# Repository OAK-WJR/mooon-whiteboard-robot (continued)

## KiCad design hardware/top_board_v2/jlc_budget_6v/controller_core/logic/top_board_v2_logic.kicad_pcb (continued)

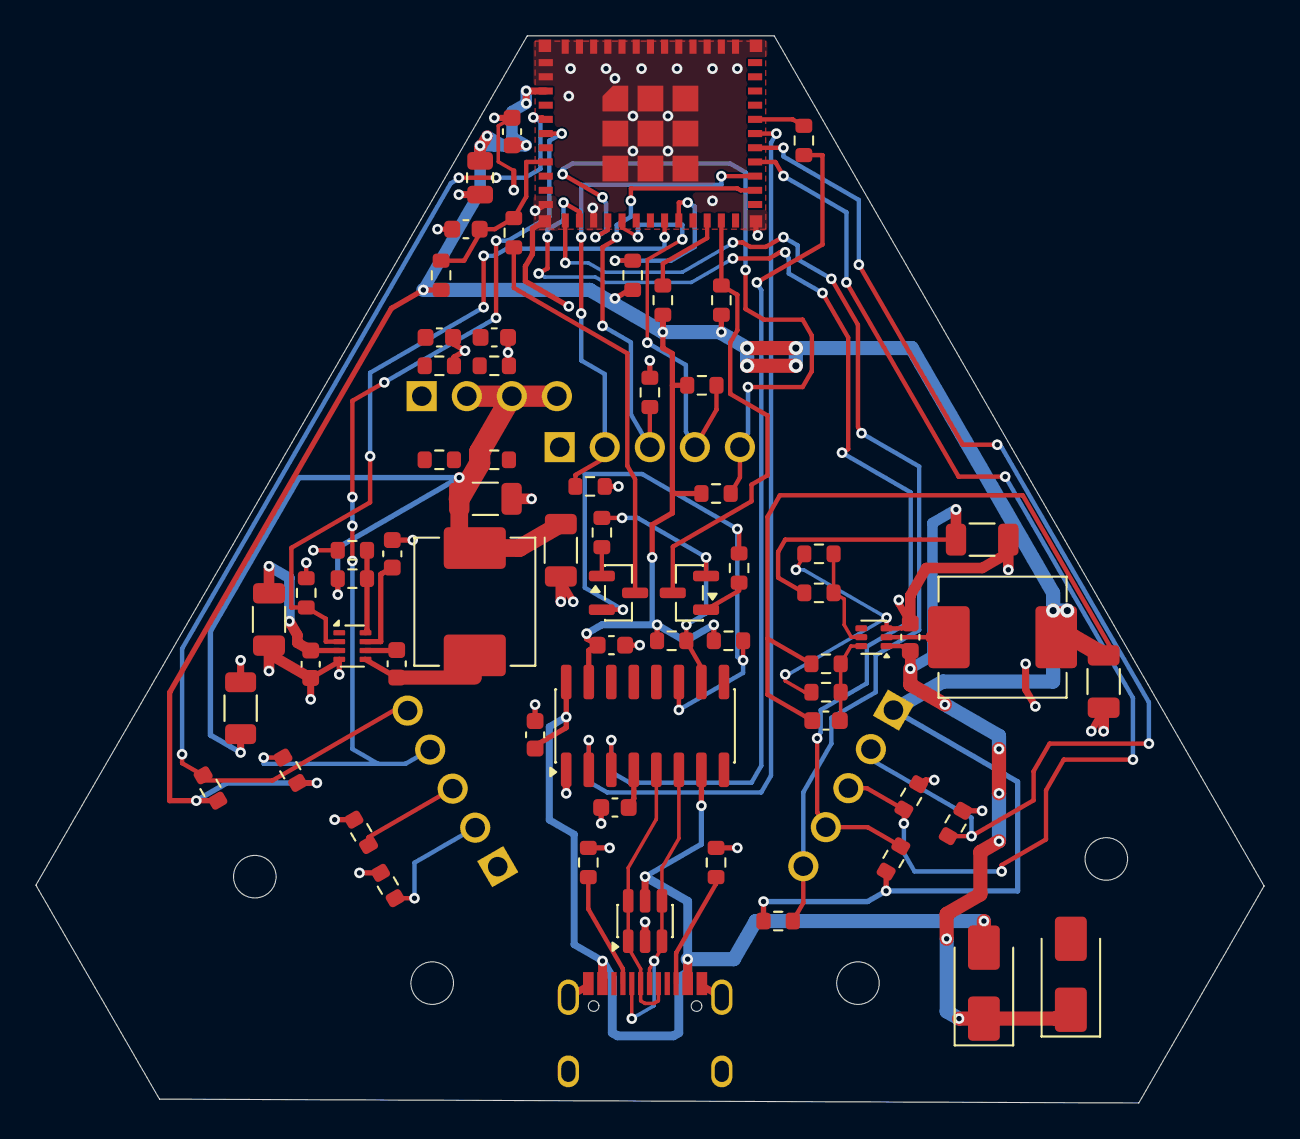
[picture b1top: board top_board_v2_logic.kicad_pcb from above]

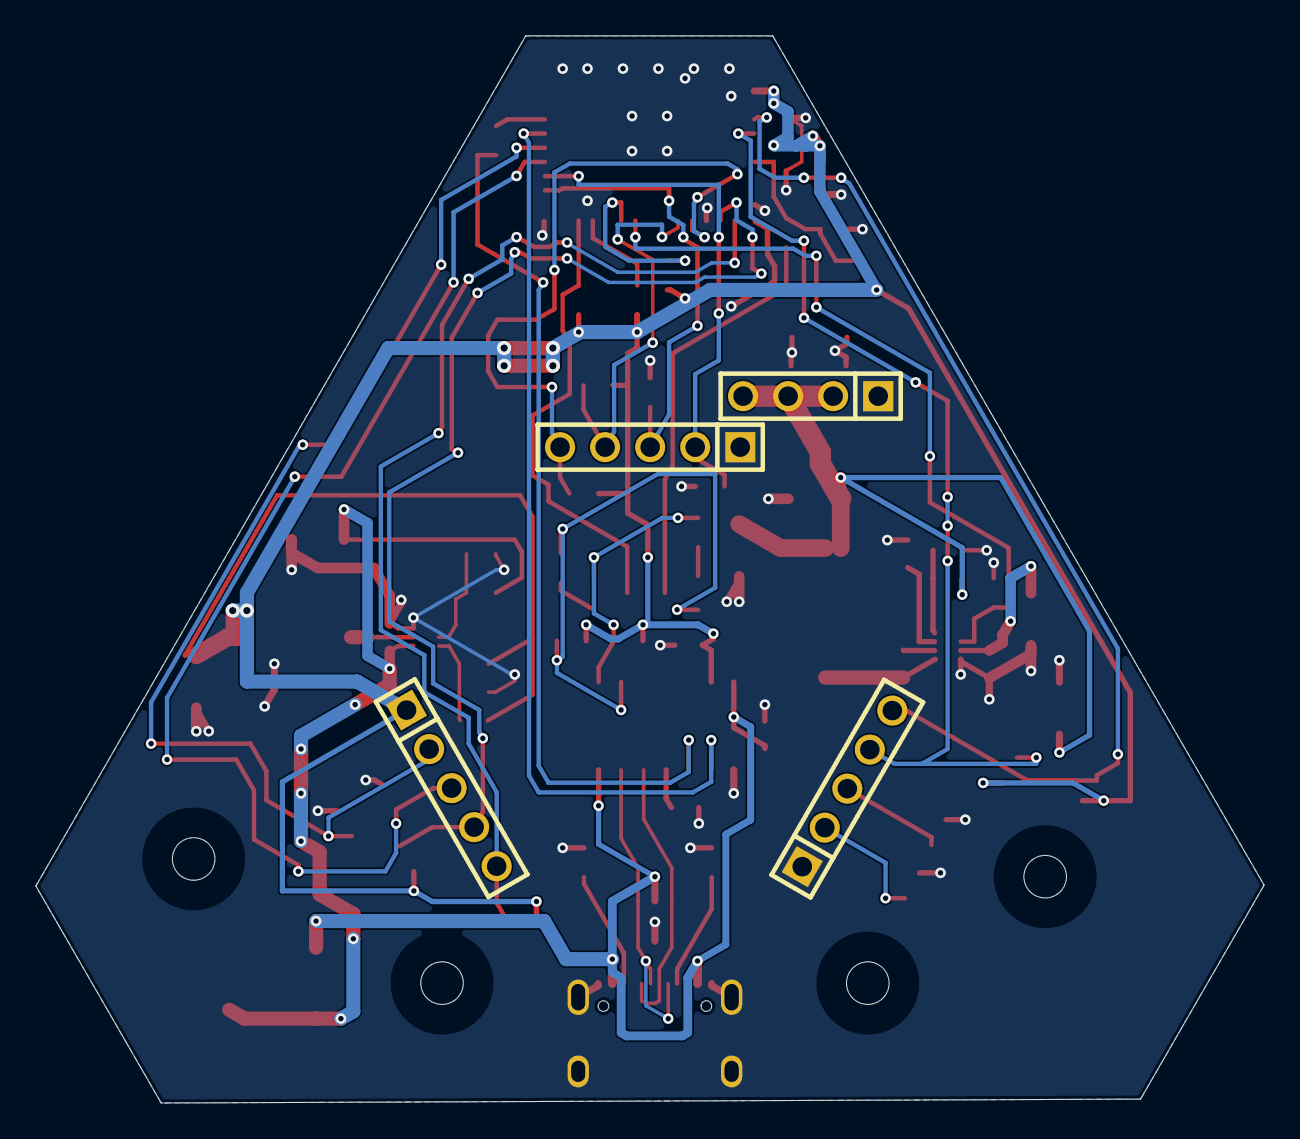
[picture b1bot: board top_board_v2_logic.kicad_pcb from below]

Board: 2 copper layers, 69.2 x 60.2 mm, 74 parts (4 on the bottom side), 45 nets.

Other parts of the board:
MH1, MH2, MH3, MH4: M2 carrier reserve: NPTH 2.4 / boss 6.0; Carrier_M2_NPTH_2.4mm_Reserve_6mm

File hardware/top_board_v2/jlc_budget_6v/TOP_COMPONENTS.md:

# List of components drawn on the top board

Exported from the current six-page KiCad netlist: 70 components per board, 350 for five boards.

Of these, 63 references have store part numbers and 7 are not yet assigned. This is a list of drawn components, not a full purchasing BOM or a finished-board quote. Having a part number also does not mean assembly and electrical verification are done.

**Scope is only the five top PCBs, the components on them and soldering.** The base board, motors, battery, charger and external accessories are not counted. The final input connector and protection are not drawn yet; undecided USB and ADC behavior may also affect the final list.

| Reference | Value in drawing | JLCPCB part number filled in | Per board | Five boards |
| --- | --- | --- | ---: | ---: |
| C1, C2, C3, C6, C8, C15, C16, C17, C20, C21 | 100n 50V X7R 10% | C14663 | 10 | 50 |
| C4 | 1u 10V X7R | TBD | 1 | 5 |
| C5 | 10u 10V X7R | TBD | 1 | 5 |
| C7, C11, C14, C18, C19 | 22u 25V X5R 10% | C12891 | 5 | 25 |
| C9 | 33p 50V C0G 5% | C1663 | 1 | 5 |
| D1, D2 | SS14 / REVIEW | C2480 | 2 | 10 |
| L1 | 2.2u 20% | C408445 | 1 | 5 |
| L2 | 4.7u 20% | C408447 | 1 | 5 |
| M0, M1, M2 | PZ254V-11-05P | C492404 | 3 | 15 |
| PWR1 | PZ254V-11-04P | C2691448 | 1 | 5 |
| Q1, Q2 | MMBT3904 | TBD | 2 | 10 |
| R1, R2 | 5.1k 1% | C23186 | 2 | 10 |
| R3, R4, R9, R10, R14, R15, R18, R19, R22, R23, R24, R25, R29, R31, R32, R34, R36 | 10k 1% | C25804 | 17 | 85 |
| R5 | 680 1% | C23228 | 1 | 5 |
| R6, R7, R12, R13, R16, R17, R20, R21 | 4.7k 1% | C23162 | 8 | 40 |
| R8 | 22k 1% | C31850 | 1 | 5 |
| R11 | 499 1% | TBD | 1 | 5 |
| R26 | 135k 1% | TBD | 1 | 5 |
| R27 | 30k 1% | C22984 | 1 | 5 |
| R28 | 64.9k 1% | C14891 | 1 | 5 |
| R30 | 470 1% 0.25W | TBD | 1 | 5 |
| R33, R35 | 120k 1% | C25808 | 2 | 10 |
| U1 | CH343G | C2844153 | 1 | 5 |
| U2 | USBLC6-2SC6 | C7519 | 1 | 5 |
| U3 | ESP32-C6-MINI-1-N4 | C5736265 | 1 | 5 |
| U4 | TPS563252DRLR | C19188399 | 1 | 5 |
| U5 | TPS62933DRLR | C3200405 | 1 | 5 |
| USB1 | TYPE-C-31-M-12 | C165948 | 1 | 5 |

Quantities are placement use, without retail minimum order quantities, loss or spares. All unquoted items stay unknown and are not counted as zero in the total.

[Footprints, fields and source file hashes per reference](top_component_inventory.json) · [Cost review](COST_REVIEW.md) · [Six-page schematic](controller_core/logic/top_board_v2_review.pdf)

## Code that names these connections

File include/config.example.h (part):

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// Note: the measured pairing of adapter-board headers to base-board sockets is crossed: M0 header -> base H2 (motor 1),
//       M1 header -> base H1 (motor 3), M2 header -> base H3 (motor 2). So pins here are bound in physical motor order,
//       [1] uses the M2 header pins and [2] uses the M1 header pins; the kinematics matrix needs no change.
// C6 pins not to use: GPIO12/13 (USB-Serial/JTAG flashing), GPIO9 (BOOT), 6/7/8/14/15/21/22 (used by the display board)

// Motor 0 = physical Motor1 (via adapter M0 header -> base H2 -> controller1)
#define MOTOR0_FI_PIN       0        // GPIO0
#define MOTOR0_BI_PIN       1        // GPIO1

// Motor 1 = physical Motor2 (via adapter M2 header -> base H3 -> controller2)
#define MOTOR1_FI_PIN       4        // GPIO4
#define MOTOR1_BI_PIN       5        // GPIO5

// Motor 2 = physical Motor3 (via adapter M1 header -> base H1 -> controller3)
#define MOTOR2_FI_PIN       2        // GPIO2
#define MOTOR2_BI_PIN       3        // GPIO3

// --- Encoder pins (A/B phase), also in physical motor order ---
#ifdef WBB_TOP_BOARD_V2
#define ENC0_A_PIN          7        // New integrated board: GPIO16 remains UART TX.
#else
#define ENC0_A_PIN          16       // GPIO16 (UART0 TXD, 100Ω series resistor on adapter board)
#endif
#define ENC0_B_PIN          17       // GPIO17 (UART0 RXD)
#define ENC1_A_PIN          20       // GPIO20  <- M2 header
#define ENC1_B_PIN          23       // GPIO23  <- M2 header
#define ENC2_A_PIN          18       // GPIO18  <- M1 header
#define ENC2_B_PIN          19       // GPIO19  <- M1 header

#else
// ===================== ESP32 (old all-in-one board, kept for fallback) =====================
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
// Motor 2 (controller3, Motor3)
#define MOTOR2_FI_PIN       27       // GPIO27 - controller3 FI (forward input)
#define MOTOR2_BI_PIN       14       // GPIO14 - controller3 BI (reverse input)

// --- Encoder pins (A/B phase) ---
// motor0 encoder (Motor1 connector) - confirmed by measurement
#define ENC0_A_PIN          34       // GPIO34 - Motor1 Enc A (input only, no internal pull-up)
#define ENC0_B_PIN          35       // GPIO35 - Motor1 Enc B (input only, no internal pull-up)
// motor1 encoder (Motor2 connector) - v2 board reroutes to GPIO22/23 (regular pins, with internal pull-up)
#define ENC1_A_PIN          22       // GPIO22 - Motor2 Enc A (internal pull-up, no external resistor)
#define ENC1_B_PIN          23       // GPIO23 - Motor2 Enc B (internal pull-up, no external resistor)
// motor2 encoder (Motor3 connector) - confirmed by measurement
#define ENC2_A_PIN          19       // GPIO19 - Motor3 Enc A
#define ENC2_B_PIN          18       // GPIO18 - Motor3 Enc B
#endif

// --- Encoder direction correction ---
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
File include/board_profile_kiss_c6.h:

#pragma once
// C6-MINI top schematic; power/PCB/harness not released.
#if !defined(WBB_TOP_BOARD_KISS_C6) || WBB_TOP_BOARD_KISS_C6 != 1
#error "Select the explicit top_board_v2_kiss_c6 environment"
#endif
#if defined(WBB_TOP_BOARD_R3) || defined(WBB_TOP_BOARD_PICO)
#error "KISS C6 cannot be combined with another board profile"
#endif
#if !defined(CONFIG_IDF_TARGET_ESP32C6) || !CONFIG_IDF_TARGET_ESP32C6 || defined(CONFIG_IDF_TARGET_ESP32S3)
#error "KISS C6 requires ESP32-C6"
#endif
#if !defined(WBB_TOP_BOARD_V2) || WBB_TOP_BOARD_V2 != 1 || defined(WBB_R3_DIAGNOSTIC) || defined(MOTOR_TEST_MODE)
#error "KISS C6 requires the gated integrated runtime"
#endif
#if !defined(ARDUINO_USB_CDC_ON_BOOT) || ARDUINO_USB_CDC_ON_BOOT != 1
#error "KISS C6 has no USB-UART bridge (CH343G removed 2026-10-29): Serial is the C6's native USB CDC"
#endif

#include <stdint.h>
namespace kiss_c6 {
constexpr const char* profile = "top_board_v2_kiss_c6_review";
// GPIO map follows the 2026-10-27 escape re-route: each header takes the module pads nearest to it.
constexpr int motorArmRequest = 0;
// Factory ADC conversion uses these pins. Divider calibration/off-state review pending.
// batterySense: VBAT divider (120k/10k). motorSense (2026-10-28 board rev): total motor current from INA180A1
// (gain 20) on the 0.1 ohm VMOT shunt R49, via 1k/100nF -> 2.0 V per A. Linear (datasheet gain error) to ~1.4 A
// (VOUT <= VS-0.5 V); the output rails near 3.27 V (~1.6 A). It is no longer VMOT.
constexpr int batterySense = 4, motorSense = 5;
// Sensor head (J1), 2026-10-29: GPIO12/13 are the native USB again, so I2C SDA moved to the GPIO15 strap (sampled
// only if the JTAG-select eFuse is burned) and SCL to GPIO16 (the ROM boot log toggles it with SDA high: no START).
// The IR LED switch moved to GPIO17, which stays quiet at boot; R25 still pulls it up (IR off).
constexpr int i2cSda = 15, i2cScl = 16, irEnableN = 17;
// USB power sense (2026-10-29): VBUS -> R52 1k -> USB_DIV -> R10 2.2k -> GND, isolated from IO8 by Q1 (2N7002, gate 3V3,
// drain USB_DIV, source IO8) with R53 100k IO8 -> 3V3. USB present: USB_DIV ~3.4 V (3.0 V at a 4.4 V sag), Q1 off, IO8 = 3.3 V.
// No USB: VBUS floats except for D1's reverse leakage (SS14, up to ~0.3 mA hot), which the stiff divider turns into <=0.66 V,
// so Q1 conducts and IO8 <= 0.72 V (< VIL 0.825 V). 3V3 off while charging: Q1 off, nothing drives the unpowered IO8.
// IO8 is a strap that only matters for manual download mode, which always has USB plugged in (so it reads high).
// The board reports "battery" vs "external_power" over USB and Wi-Fi; whether the IP2326 is still charging is not
// observable (no charger status pin reaches the MCU). Charging draws ~1.2 A at 5 V (0.6 A into the 2S pack). Since
// 2026-10-30 a CC gate (LM393 U8 vs a 0.65 V CJ431 threshold, Q2 on IP2326 EN) enables charging only on a USB-C source
// advertising >=1.5 A; a Default-USB source or a USB-A cable powers the board but does not charge.
constexpr int usbPowerSense = 8;
struct MotorPins { uint8_t fi, bi, encA, encB, physical; const char* header; };
constexpr MotorPins headers[] = {
    {22, 23, 20, 21, 1, "M0"},
    {1, 6, 2, 3, 3, "M1"},
    {14, 7, 19, 18, 2, "M2"},
};
constexpr int physicalOrder[] = {0, 2, 1};
constexpr bool isMotorPin(int pin) {
    for (const auto& p : headers) if (pin == p.fi || pin == p.bi) return true;
    return false;
}
constexpr bool isMotorPair(int fi, int bi) {
    for (const auto& p : headers) if (fi == p.fi && bi == p.bi) return true;
    return false;
}
constexpr bool pinsAreDistinct() {
    const int used[] = {headers[0].fi,headers[0].bi,headers[0].encA,headers[0].encB,
                        headers[1].fi,headers[1].bi,headers[1].encA,headers[1].encB,
                        headers[2].fi,headers[2].bi,headers[2].encA,headers[2].encB,i2cScl,irEnableN,
                        motorArmRequest,batterySense,motorSense};
    for (unsigned i=0; i<sizeof(used)/sizeof(used[0]); ++i) {
        if (used[i]<0 || used[i]>23 || used[i]==8 || used[i]==9 ||
            used[i]==10 || used[i]==11 || used[i]==12 || used[i]==13 || used[i]==15) return false;
        for (unsigned j=0; j<i; ++j) if (used[i]==used[j]) return false;
    }
    return true;
}
static_assert(pinsAreDistinct(), "KISS C6 pins alias reserved or application pins");
static_assert(i2cSda == 15 && !isMotorPin(i2cSda) && i2cSda != i2cScl && i2cSda != irEnableN,
              "SDA is the only application pin allowed on the GPIO15 strap");
static_assert(usbPowerSense == 8 && !isMotorPin(usbPowerSense), "USB power sense is the only input on the GPIO8 strap");
} // namespace kiss_c6

#undef MOTOR0_FI_PIN
#undef MOTOR0_BI_PIN
#undef MOTOR1_FI_PIN
#undef MOTOR1_BI_PIN
#undef MOTOR2_FI_PIN
#undef MOTOR2_BI_PIN
#undef ENC0_A_PIN
#undef ENC0_B_PIN
#undef ENC1_A_PIN
#undef ENC1_B_PIN
#undef ENC2_A_PIN
#undef ENC2_B_PIN
#define MOTOR0_FI_PIN kiss_c6::headers[0].fi
#define MOTOR0_BI_PIN kiss_c6::headers[0].bi
#define MOTOR1_FI_PIN kiss_c6::headers[2].fi
#define MOTOR1_BI_PIN kiss_c6::headers[2].bi
#define MOTOR2_FI_PIN kiss_c6::headers[1].fi
#define MOTOR2_BI_PIN kiss_c6::headers[1].bi
#define ENC0_A_PIN kiss_c6::headers[0].encA
#define ENC0_B_PIN kiss_c6::headers[0].encB
#define ENC1_A_PIN kiss_c6::headers[2].encA
#define ENC1_B_PIN kiss_c6::headers[2].encB
#define ENC2_A_PIN kiss_c6::headers[1].encA
#define ENC2_B_PIN kiss_c6::headers[1].encB
// Raw count orientation; final motor gearing and harness calibration pending.
#undef ENCODER_DIR_M0
#undef ENCODER_DIR_M1
#undef ENCODER_DIR_M2
#define ENCODER_DIR_M0 (+1)
#define ENCODER_DIR_M1 (+1)
#define ENCODER_DIR_M2 (+1)

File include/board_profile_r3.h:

#pragma once
// Review profile for kicad/r3_system/core_contract.json, not a released board ID.
// GPIO21 is a request with a 10k pulldown; it is NOT a motor power disconnect.
#if !defined(WBB_TOP_BOARD_R3) || WBB_TOP_BOARD_R3 != 1
#error "Select the explicit R3 review build environment"
#endif
#if !defined(CONFIG_IDF_TARGET_ESP32C6) || !CONFIG_IDF_TARGET_ESP32C6
#error "R3 requires ESP32-C6"
#endif
#if !defined(ARDUINO_USB_CDC_ON_BOOT) || ARDUINO_USB_CDC_ON_BOOT != 0
#error "R3 CP2102N requires UART0 Serial (ARDUINO_USB_CDC_ON_BOOT=0)"
#endif

#include <stdint.h>
namespace r3 {
constexpr const char* profile = "top_board_v2_r3_review";
constexpr int uartTx = 16, uartRx = 17;
constexpr int motorArmRequest = 21;
constexpr int watchdogHeartbeat = 12;
constexpr int i2cSda = 14, i2cScl = 22;
constexpr int led = 15;
// GPIO12 is wired to the external watchdog, reserved for checked open-drain service.
// Its pulse service is not yet implemented; GPIO13 remains NC.
// J2 pin3 is UART RX17, not AUX GPIO6.
// No AUX output or charger/I2C initialization is provided by this profile.
struct MotorPins { uint8_t fi, bi, encA, encB, physical; const char* header; };
// Diagnostic display order is by header, intentionally different from kinematics.
constexpr MotorPins headers[] = {
    {0, 1, 7, 6, 1, "M0"},
    {2, 3, 18, 19, 3, "M1"},
    {4, 5, 20, 23, 2, "M2"},
};
constexpr int physicalOrder[] = {0, 2, 1}; // Physical Motor1/2/3 = M0/M2/M1.
constexpr bool pinsAreDistinct() {
    const int used[] = {0, 1, 7, 6, 2, 3, 18, 19, 4, 5, 20, 23,
                        uartTx, uartRx, motorArmRequest, watchdogHeartbeat, i2cSda, i2cScl, led};
    for (unsigned i = 0; i < sizeof(used) / sizeof(used[0]); ++i) {
        if (used[i] == 13 || used[i] == 8 || used[i] == 9) return false;
        for (unsigned j = 0; j < i; ++j) if (used[i] == used[j]) return false;
    }
    return true;
}
static_assert(pinsAreDistinct(), "R3 pins must not alias UART, NC or boot straps");
} // namespace r3

// Override even a stale board configuration, in every firmware translation unit.
// The R3 environments pre-include public defaults; private config.h stays untouched.
#undef MOTOR0_FI_PIN
#undef MOTOR0_BI_PIN
#undef MOTOR1_FI_PIN
#undef MOTOR1_BI_PIN
#undef MOTOR2_FI_PIN
#undef MOTOR2_BI_PIN
#undef ENC0_A_PIN
#undef ENC0_B_PIN
#undef ENC1_A_PIN
#undef ENC1_B_PIN
#undef ENC2_A_PIN
#undef ENC2_B_PIN
#define MOTOR0_FI_PIN r3::headers[0].fi
#define MOTOR0_BI_PIN r3::headers[0].bi
#define MOTOR1_FI_PIN r3::headers[2].fi
#define MOTOR1_BI_PIN r3::headers[2].bi
#define MOTOR2_FI_PIN r3::headers[1].fi
#define MOTOR2_BI_PIN r3::headers[1].bi
#define ENC0_A_PIN r3::headers[0].encA
#define ENC0_B_PIN r3::headers[0].encB
#define ENC1_A_PIN r3::headers[2].encA
#define ENC1_B_PIN r3::headers[2].encB
#define ENC2_A_PIN r3::headers[1].encA
#define ENC2_B_PIN r3::headers[1].encB
